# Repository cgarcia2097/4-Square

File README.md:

# 4-Square
Repository for 4-Square PCB

### Bill of Materials
- List of materials found here: https://github.com/cgarcia2097/4-Square/blob/master/16-key%20Pro%20Micro%20Keypad/BOM.xlsx

### Schematics
- Schematics: https://github.com/cgarcia2097/4-Square/blob/master/16-key%20Pro%20Micro%20Keypad/Simple/16-key%20Pro%20Micro.sch
- Board: https://github.com/cgarcia2097/4-Square/blob/master/16-key%20Pro%20Micro%20Keypad/Simple/16-key%20Pro%20Micro.brd

As for CAM files, create them from the brd files. Gerbers here may not be up to date.

### Discussion
Threads: https://geekhack.org/index.php?topic=97625.0

## To-do:
- Assembly guide 
- PCB Redesign - flip the Pro Micro 
- Clean repo of unnecessary files

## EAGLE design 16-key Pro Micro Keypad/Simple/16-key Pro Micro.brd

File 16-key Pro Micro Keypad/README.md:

# When programming the controller 

## Creating the Arduino environment:
Since this PCB uses a Pro Micro for its controller, one must to go Sparkfun's Pro Micro installation tutorial and install drivers for the Pro Micro. Afterwards, in `Tools` -> `Boards`, select `Sparkfun Pro Micro`

## Using the Keyboard and Bounce libraries:
When making edits to the code given or writing from scratch, please use the `Keyboard.h` and `Bounce2.h` libraries. The Keyboard library handles the keyboard functionality, while the Bounce2 library handles switch debounce.

## To-do
* Build Guides
* Code cleanup and explanation
* Repository organization
* Photos/videos of the keypad
* Let me know

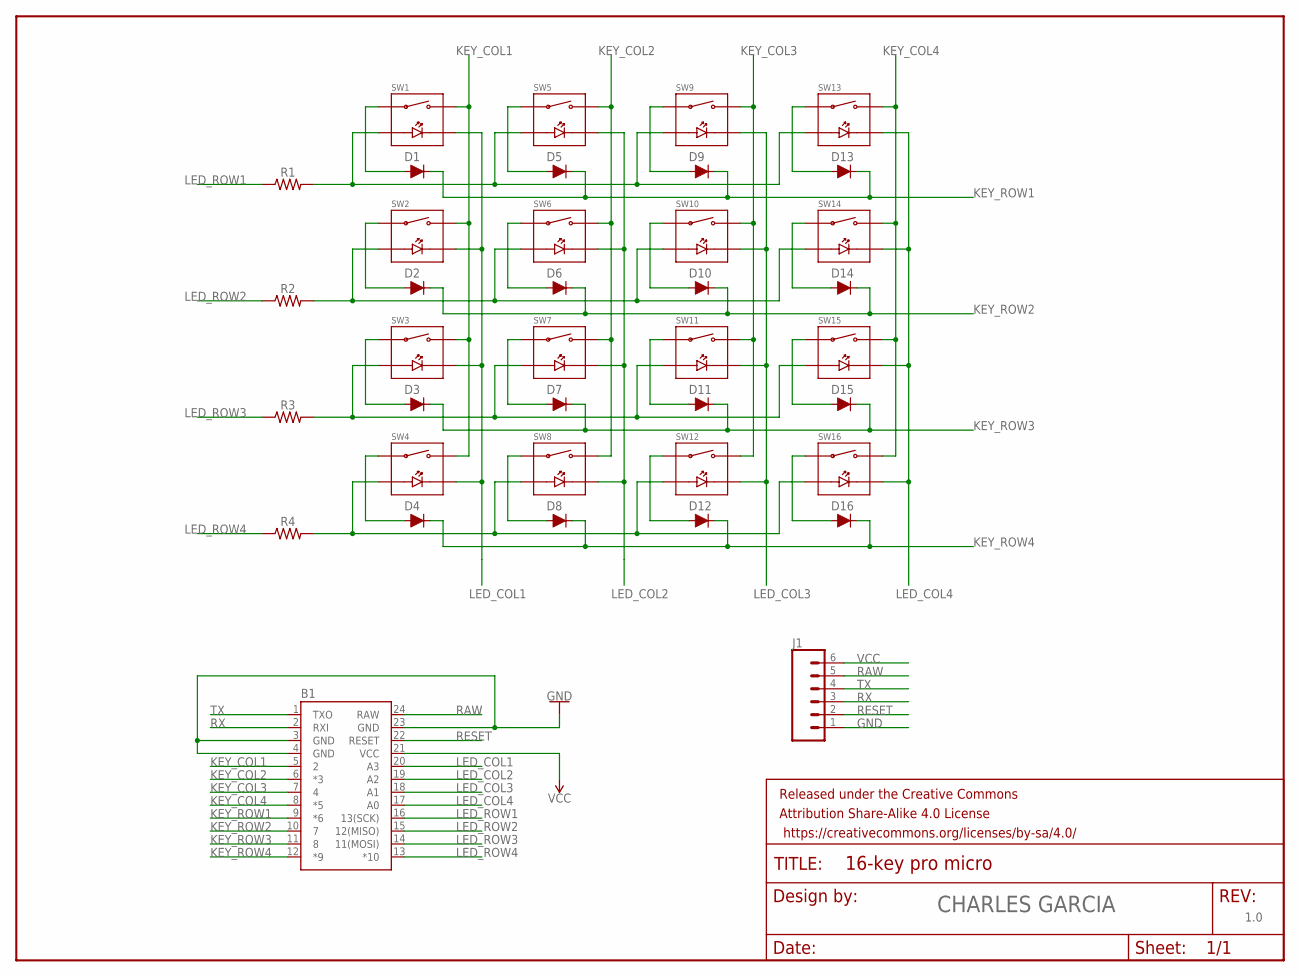
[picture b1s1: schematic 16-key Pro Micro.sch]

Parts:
B1: SPARKFUN_PRO_MICRO
D1, D2, D3, D4, D5, D6, D7, D8, D9, D10, D11, D12, D13, D14, D15, D16: DIODE-1N4148
FRAME1: FRAME-LETTER; CREATIVE_COMMONS
J1: CONN_06SILK_FEMALE_PTH; 1X06
R1, R2, R3, R4: AXIAL-0.3
SW1, SW2, SW3, SW4, SW5, SW6, SW7, SW8, SW9, SW10, SW11, SW12, SW13, SW14, SW15, SW16: CHERRY_MX_PCB_LED; MX_PCB_MOUNT_LED

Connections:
GND: B1.3 (GND), B1.4 (GND), B1.23 (GND), J1.1
KEY_COL1: B1.5 (2), SW1.SW_OUT, SW2.SW_OUT, SW3.SW_OUT, SW4.SW_OUT
KEY_COL2: B1.6 (*3), SW5.SW_OUT, SW6.SW_OUT, SW7.SW_OUT, SW8.SW_OUT
KEY_COL3: B1.7 (4), SW9.SW_OUT, SW10.SW_OUT, SW11.SW_OUT, SW12.SW_OUT
KEY_COL4: B1.8 (*5), SW13.SW_OUT, SW14.SW_OUT, SW15.SW_OUT, SW16.SW_OUT
KEY_ROW1: B1.9 (*6), D1.C, D5.C, D9.C, D13.C
KEY_ROW2: B1.10 (7), D2.C, D6.C, D10.C, D14.C
KEY_ROW3: B1.11 (8), D3.C, D7.C, D11.C, D15.C
KEY_ROW4: B1.12 (*9), D4.C, D8.C, D12.C, D16.C
LED_COL1: B1.20 (A3), SW1.LED_OUT, SW2.LED_OUT, SW3.LED_OUT, SW4.LED_OUT
LED_COL2: B1.19 (A2), SW5.LED_OUT, SW6.LED_OUT, SW7.LED_OUT, SW8.LED_OUT
LED_COL3: B1.18 (A1), SW9.LED_OUT, SW10.LED_OUT, SW11.LED_OUT, SW12.LED_OUT
LED_COL4: B1.17 (A0), SW13.LED_OUT, SW14.LED_OUT, SW15.LED_OUT, SW16.LED_OUT
LED_ROW1: B1.16 (13(SCK)), R1.P$1 (1)
LED_ROW2: B1.15 (12(MISO)), R2.P$1 (1)
LED_ROW3: B1.14 (11(MOSI)), R3.P$1 (1)
LED_ROW4: B1.13 (*10), R4.P$1 (1)
unnamed: D1.A, SW1.SW_IN
unnamed: D2.A, SW2.SW_IN
unnamed: D3.A, SW3.SW_IN
unnamed: D4.A, SW4.SW_IN
unnamed: D5.A, SW5.SW_IN
unnamed: D6.A, SW6.SW_IN
unnamed: D7.A, SW7.SW_IN
unnamed: D8.A, SW8.SW_IN
unnamed: D9.A, SW9.SW_IN
unnamed: D10.A, SW10.SW_IN
unnamed: D11.A, SW11.SW_IN
unnamed: D12.A, SW12.SW_IN
unnamed: D13.A, SW13.SW_IN
unnamed: D14.A, SW14.SW_IN
unnamed: D15.A, SW15.SW_IN
unnamed: D16.A, SW16.SW_IN
unnamed: R1.P$2 (2), SW1.LED_IN, SW5.LED_IN, SW9.LED_IN, SW13.LED_IN
unnamed: R2.P$2 (2), SW2.LED_IN, SW6.LED_IN, SW10.LED_IN, SW14.LED_IN
unnamed: R3.P$2 (2), SW3.LED_IN, SW7.LED_IN, SW11.LED_IN, SW15.LED_IN
unnamed: R4.P$2 (2), SW4.LED_IN, SW8.LED_IN, SW12.LED_IN, SW16.LED_IN
RAW: B1.24 (RAW), J1.5
RESET: B1.22 (RESET), J1.2
RX: B1.2 (RXI), J1.3
TX: B1.1 (TXO), J1.4
VCC: B1.21 (VCC), J1.6

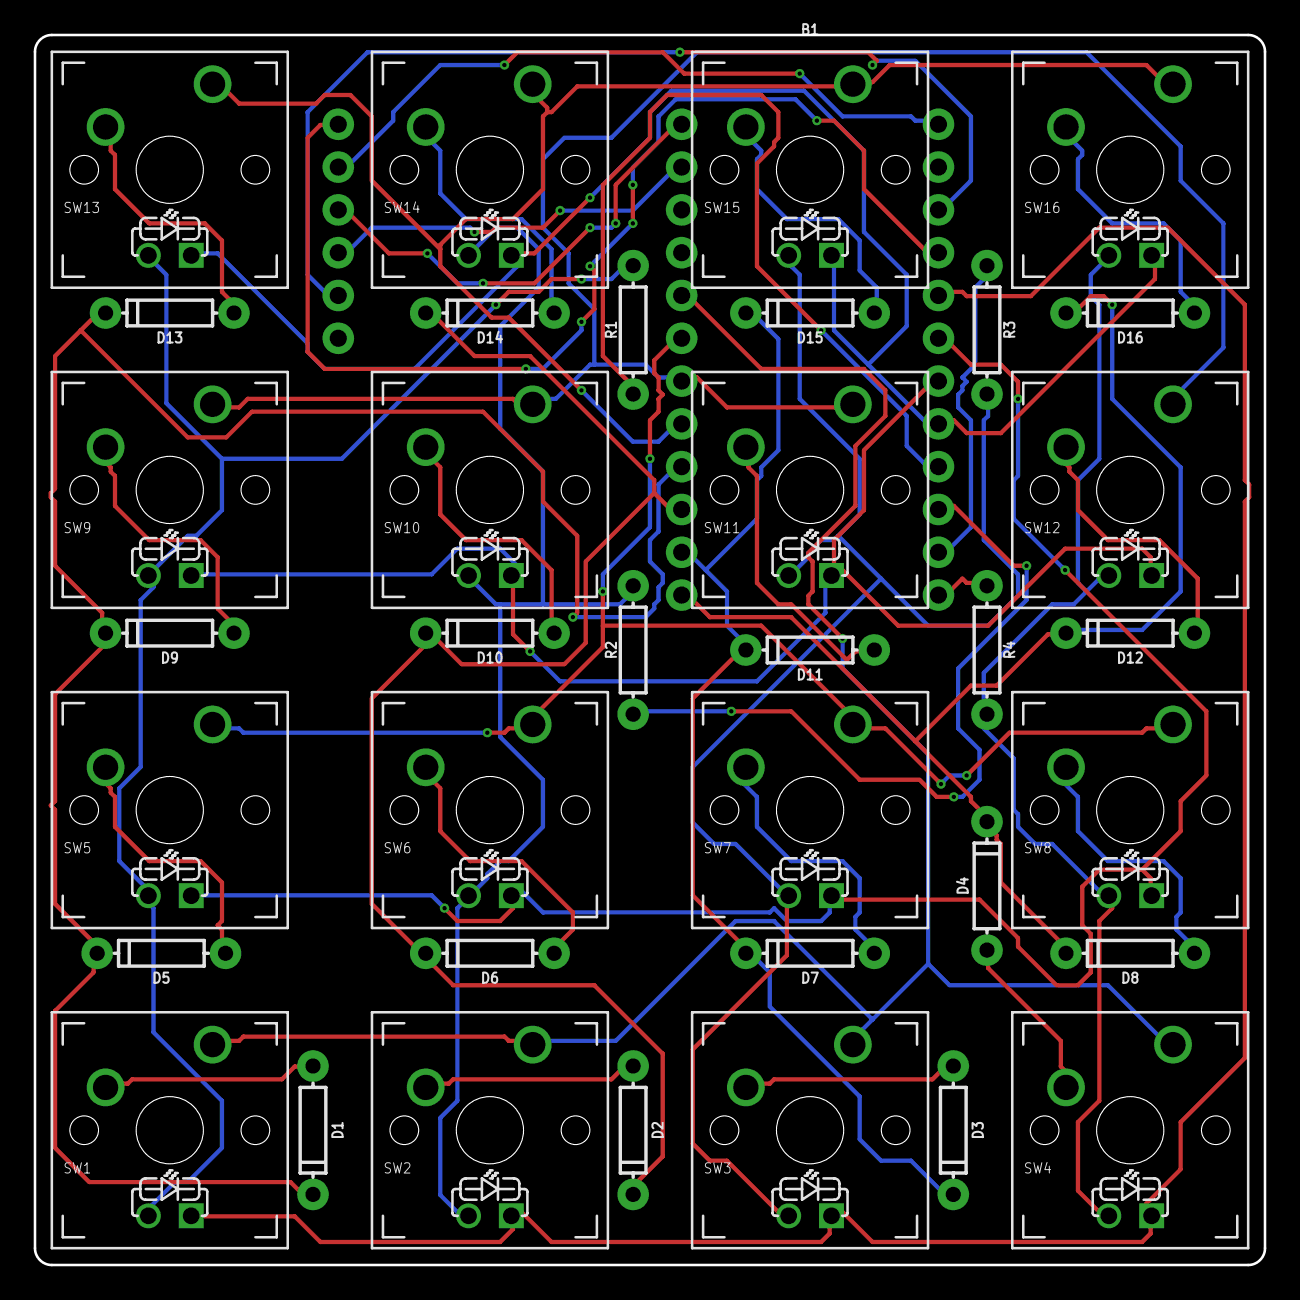
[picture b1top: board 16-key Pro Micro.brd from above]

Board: 2 copper layers, 73.0 x 73.0 mm, 39 parts (1 on the bottom side), 42 nets.

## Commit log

2018-10-25 Add files via upload
    All files used in the project
2019-03-19 Added sketch for testing

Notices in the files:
parts and their libraries:
SparkFun-Boards: Licensing: Creative Commons ShareAlike 4.0 International - https://creativecommons.org/licenses/by-sa/4.0
SparkFun-Aesthetics: Released under the Creative Commons Attribution Share-Alike 4.0 License
SparkFun-Aesthetics: https://creativecommons.org/licenses/by-sa/4.0
